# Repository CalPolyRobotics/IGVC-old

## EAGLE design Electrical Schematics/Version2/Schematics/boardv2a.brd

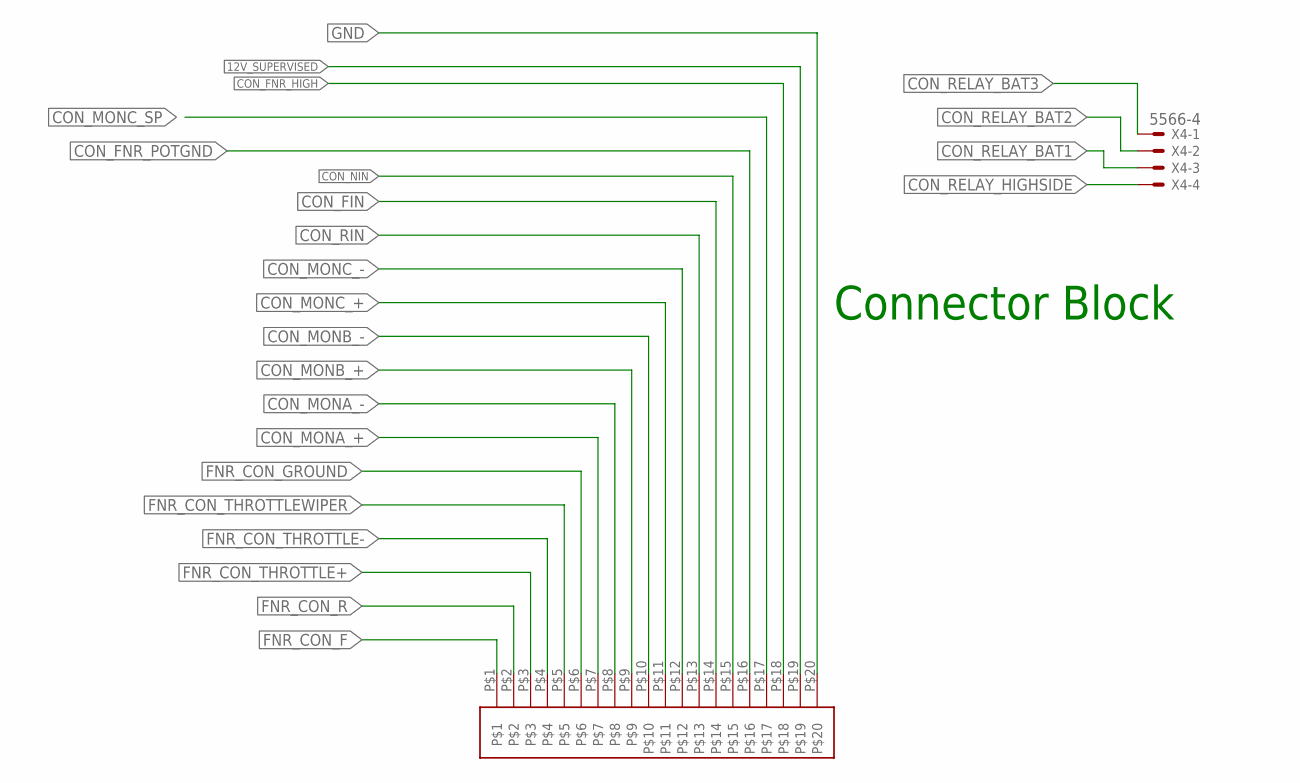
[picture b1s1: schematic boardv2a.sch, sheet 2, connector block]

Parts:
U$5: 34830-2001
X4: 5566-4

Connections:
12V_SUPERVISED: U$5.P$19; also elsewhere on the board
CON_FIN: U$5.P$14; also elsewhere on the board
CON_FNR_HIGH: U$5.P$18; also elsewhere on the board
CON_FNR_POTGND: U$5.P$16; also elsewhere on the board
CON_MONA_+: U$5.P$7; also elsewhere on the board
CON_MONA_-: U$5.P$8; also elsewhere on the board
CON_MONB_+: U$5.P$9; also elsewhere on the board
CON_MONB_-: U$5.P$10; also elsewhere on the board
CON_MONC_+: U$5.P$11; also elsewhere on the board
CON_MONC_-: U$5.P$12; also elsewhere on the board
CON_MONC_SP: U$5.P$17; also elsewhere on the board
CON_NIN: U$5.P$15; also elsewhere on the board
CON_RELAY_BAT1: X4.3; also elsewhere on the board
CON_RELAY_BAT2: X4.2; also elsewhere on the board
CON_RELAY_BAT3: X4.1; also elsewhere on the board
CON_RELAY_HIGHSIDE: X4.4
CON_RIN: U$5.P$13; also elsewhere on the board
FNR_CON_F: U$5.P$1; also elsewhere on the board
FNR_CON_GROUND: U$5.P$6
FNR_CON_R: U$5.P$2; also elsewhere on the board
FNR_CON_THROTTLE+: U$5.P$3; also elsewhere on the board
FNR_CON_THROTTLE-: U$5.P$4; also elsewhere on the board
FNR_CON_THROTTLEWIPER: U$5.P$5; also elsewhere on the board
GND: U$5.P$20; also elsewhere on the board

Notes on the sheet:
Connector Block

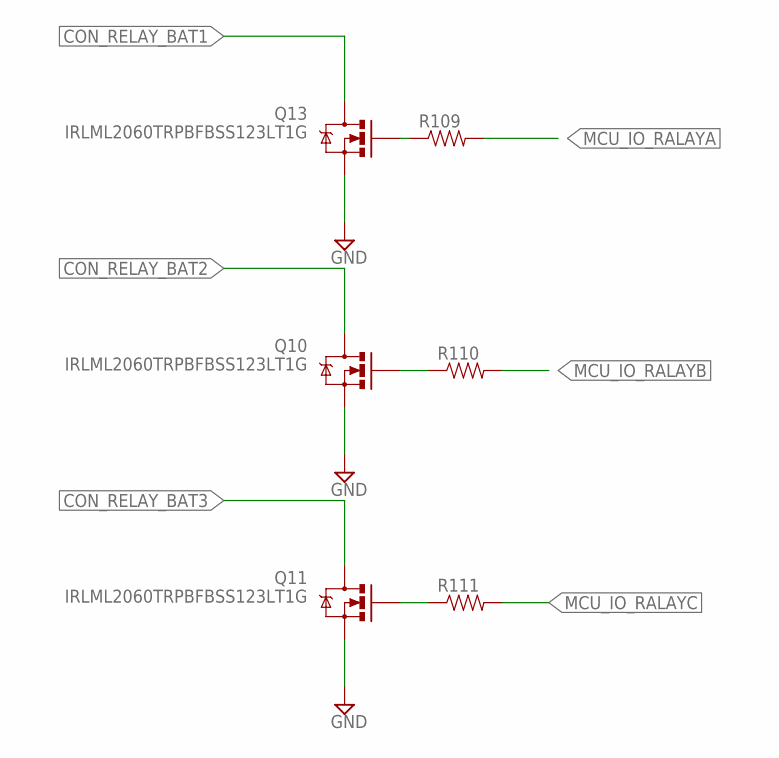
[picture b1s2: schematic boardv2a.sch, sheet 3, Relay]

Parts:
Q10, Q11, Q13: IRLML2060TRPBFBSS123LT1G; SOT23-3
R109, R110, R111: RESISTOR0603-RES; 0603-RES

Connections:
CON_RELAY_BAT1: Q13.3 (D); also elsewhere on the board
CON_RELAY_BAT2: Q10.3 (D); also elsewhere on the board
CON_RELAY_BAT3: Q11.3 (D); also elsewhere on the board
GND: Q10.2 (S), Q11.2 (S), Q13.2 (S); also elsewhere on the board
MCU_IO_RALAYA: R109.2; also elsewhere on the board
MCU_IO_RALAYB: R110.2; also elsewhere on the board
MCU_IO_RALAYC: R111.2; also elsewhere on the board
unnamed: Q13.1 (G), R109.1
unnamed: Q11.1 (G), R111.1
unnamed: Q10.1 (G), R110.1

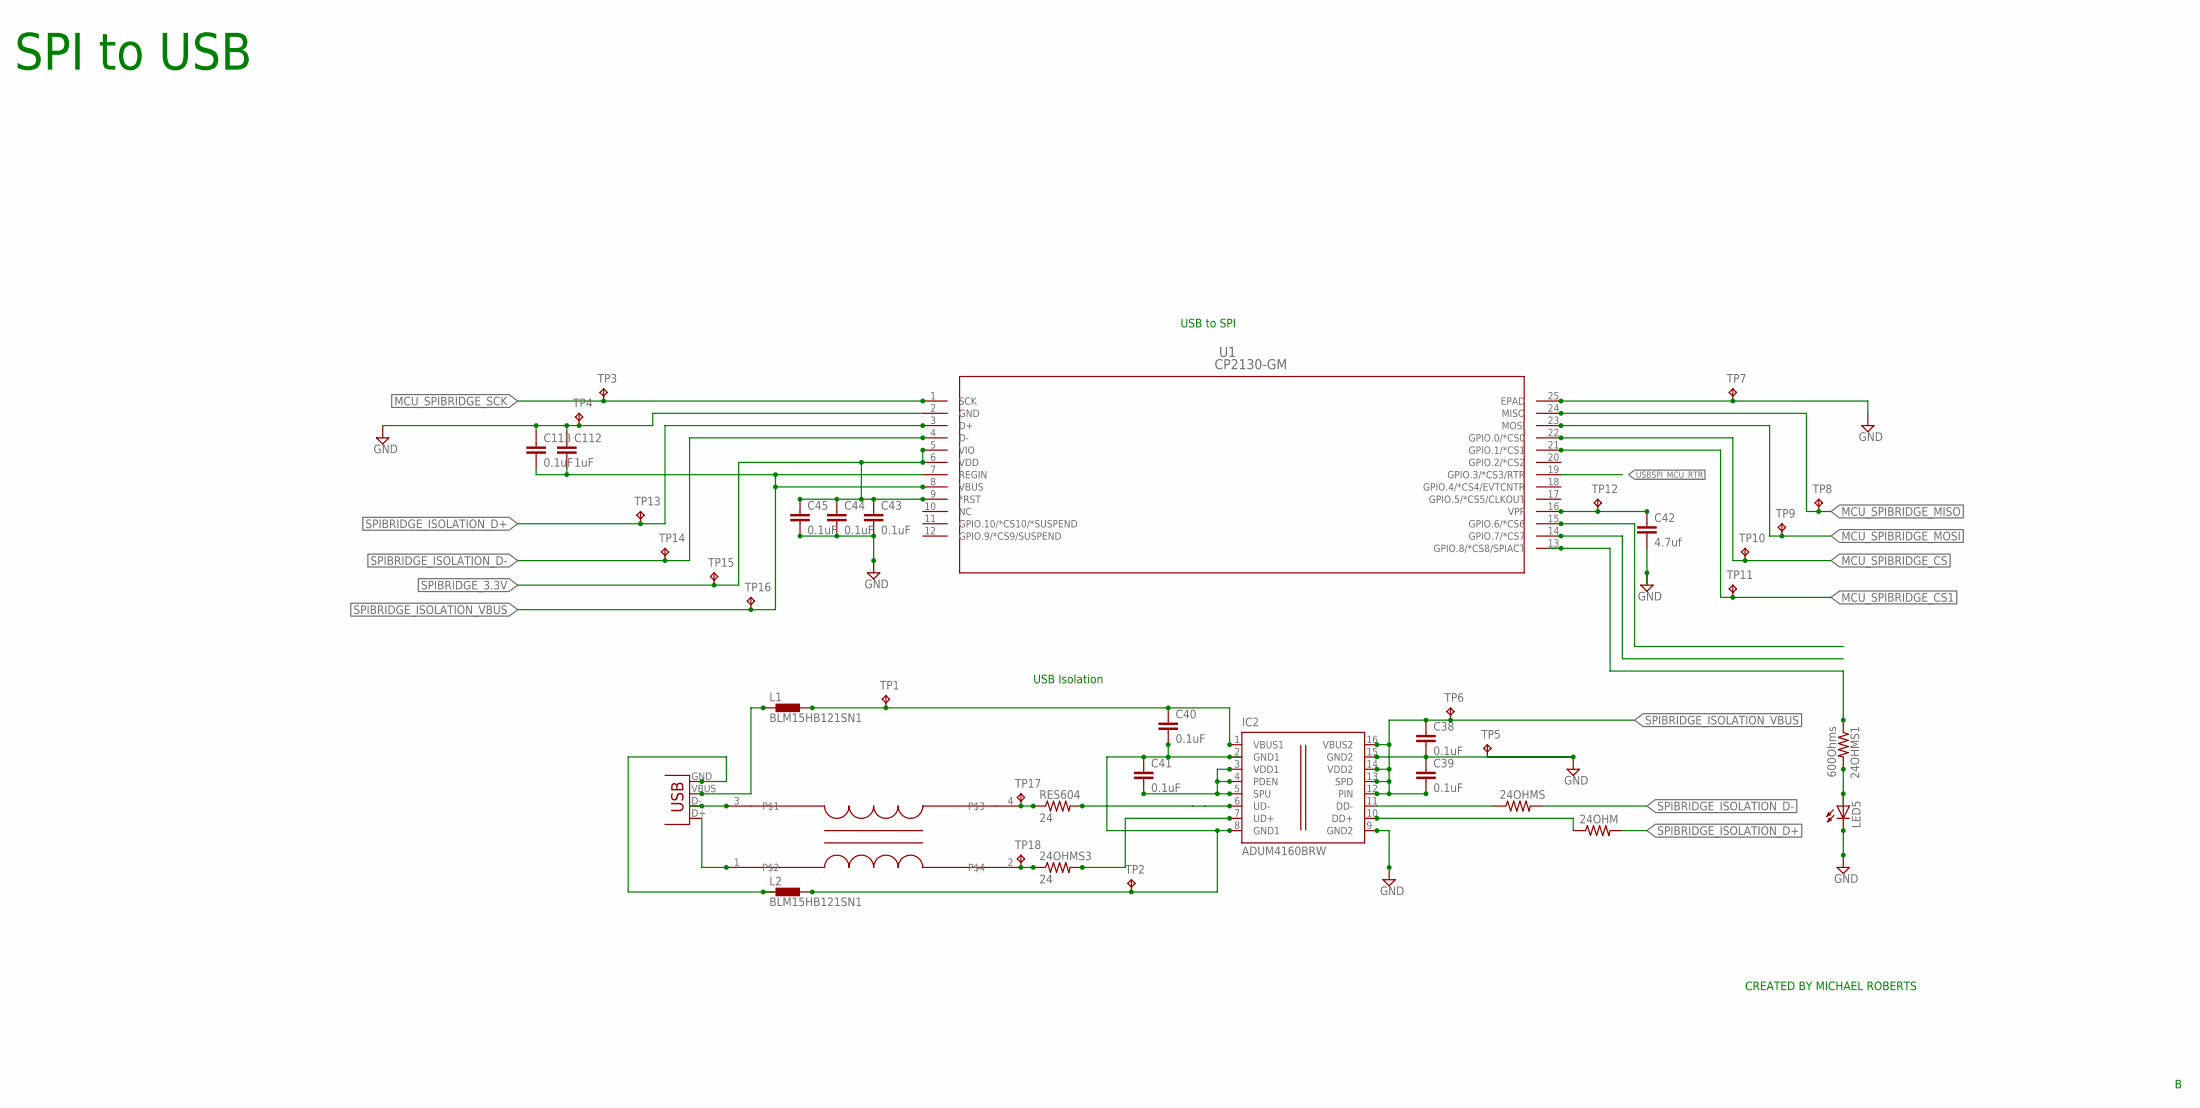
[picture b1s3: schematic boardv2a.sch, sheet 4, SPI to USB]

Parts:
24OHM, 24OHMS: RESISTOR0603-RES; 0603-RES
24OHMS1: 600Ohms; 0603-RES
24OHMS3: 24; 0603-RES
C38, C39, C40, C41, C43, C44, C45, C113: 0.1uF; C0603
C42: 4.7uf; C0603
C112: 1uF; C0603
IC2: ADUM4160BRW; SO16W
JP81: USB-B; USB-B-PTH
L1, L2: BLM15HB121SN1; 0402
LED5: LED_E; LED_1206
RES604: 24; 0603-RES
TP1, TP2, TP3, TP4, TP5, TP6, TP7, TP12, TP13, TP14, TP15, TP16: TPB1,27; B1,27
TP8, TP9, TP10, TP11, TP17, TP18: TPB2,54; B2,54
U1: CP2130-GM; QFN24_4X4
U$8: ACM3225-2P

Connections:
GND: C38.2, C39.1, C42.2, C43.2, C44.2, C45.2, C112.1, C113.1, IC2.9 (GND2), IC2.15 (GND2), LED5.C, TP4.TP, TP5.TP, TP7.TP, U1.2 (GND), U1.25 (EPAD); also elsewhere on the board
MCU_SPIBRIDGE_CS: TP10.TP, U1.22 (GPIO.0/*CS0); also elsewhere on the board
MCU_SPIBRIDGE_CS1: TP11.TP, U1.21 (GPIO.1/*CS1)
MCU_SPIBRIDGE_MISO: TP8.TP, U1.24 (MISO); also elsewhere on the board
MCU_SPIBRIDGE_MOSI: TP9.TP, U1.23 (MOSI); also elsewhere on the board
MCU_SPIBRIDGE_SCK: TP3.TP, U1.1 (SCK); also elsewhere on the board
unnamed: 24OHMS.1, IC2.11 (DD-)
unnamed: 24OHMS3.2, IC2.7 (UD+)
unnamed: C40.2, C41.1, IC2.2 (GND1), IC2.8 (GND1), L2.2, TP2.TP
unnamed: C40.1, IC2.1 (VBUS1), L1.2, TP1.TP
unnamed: JP81.D-, U$8.3
unnamed: JP81.D+, U$8.1
unnamed: JP81.GND, L2.1
unnamed: C41.2, IC2.3 (VDD1), IC2.4 (PDEN), IC2.5 (SPU)
unnamed: C42.1, TP12.TP, U1.16 (VPP)
unnamed: JP81.VBUS, L1.1
unnamed: 24OHMS1.1, U1.13 (GPIO.8/*CS8/SPIACT)
unnamed: 24OHMS1.2, LED5.A
unnamed: IC2.6 (UD-), RES604.2
unnamed: RES604.1, TP17.TP, U$8.4
unnamed: 24OHMS3.1, TP18.TP, U$8.2
unnamed: 24OHM.1, IC2.10 (DD+)
SPIBRIDGE_3.3V: C43.1, C44.1, C45.1, TP15.TP, U1.5 (VIO), U1.6 (VDD), U1.9 (*RST)
SPIBRIDGE_ISOLATION_D+: 24OHM.2, TP13.TP, U1.3 (D+)
SPIBRIDGE_ISOLATION_D-: 24OHMS.2, TP14.TP, U1.4 (D-)
SPIBRIDGE_ISOLATION_VBUS: C38.1, C39.2, C112.2, C113.2, IC2.12 (PIN), IC2.13 (SPD), IC2.14 (VDD2), IC2.16 (VBUS2), TP6.TP, TP16.TP, U1.7 (REGIN), U1.8 (VBUS)
USBSPI_MCU_RTR: U1.19 (GPIO.3/*CS3/RTR); also elsewhere on the board

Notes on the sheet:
USB Isolation
USB to SPI
SPI to USB
CREATED BY MICHAEL ROBERTS

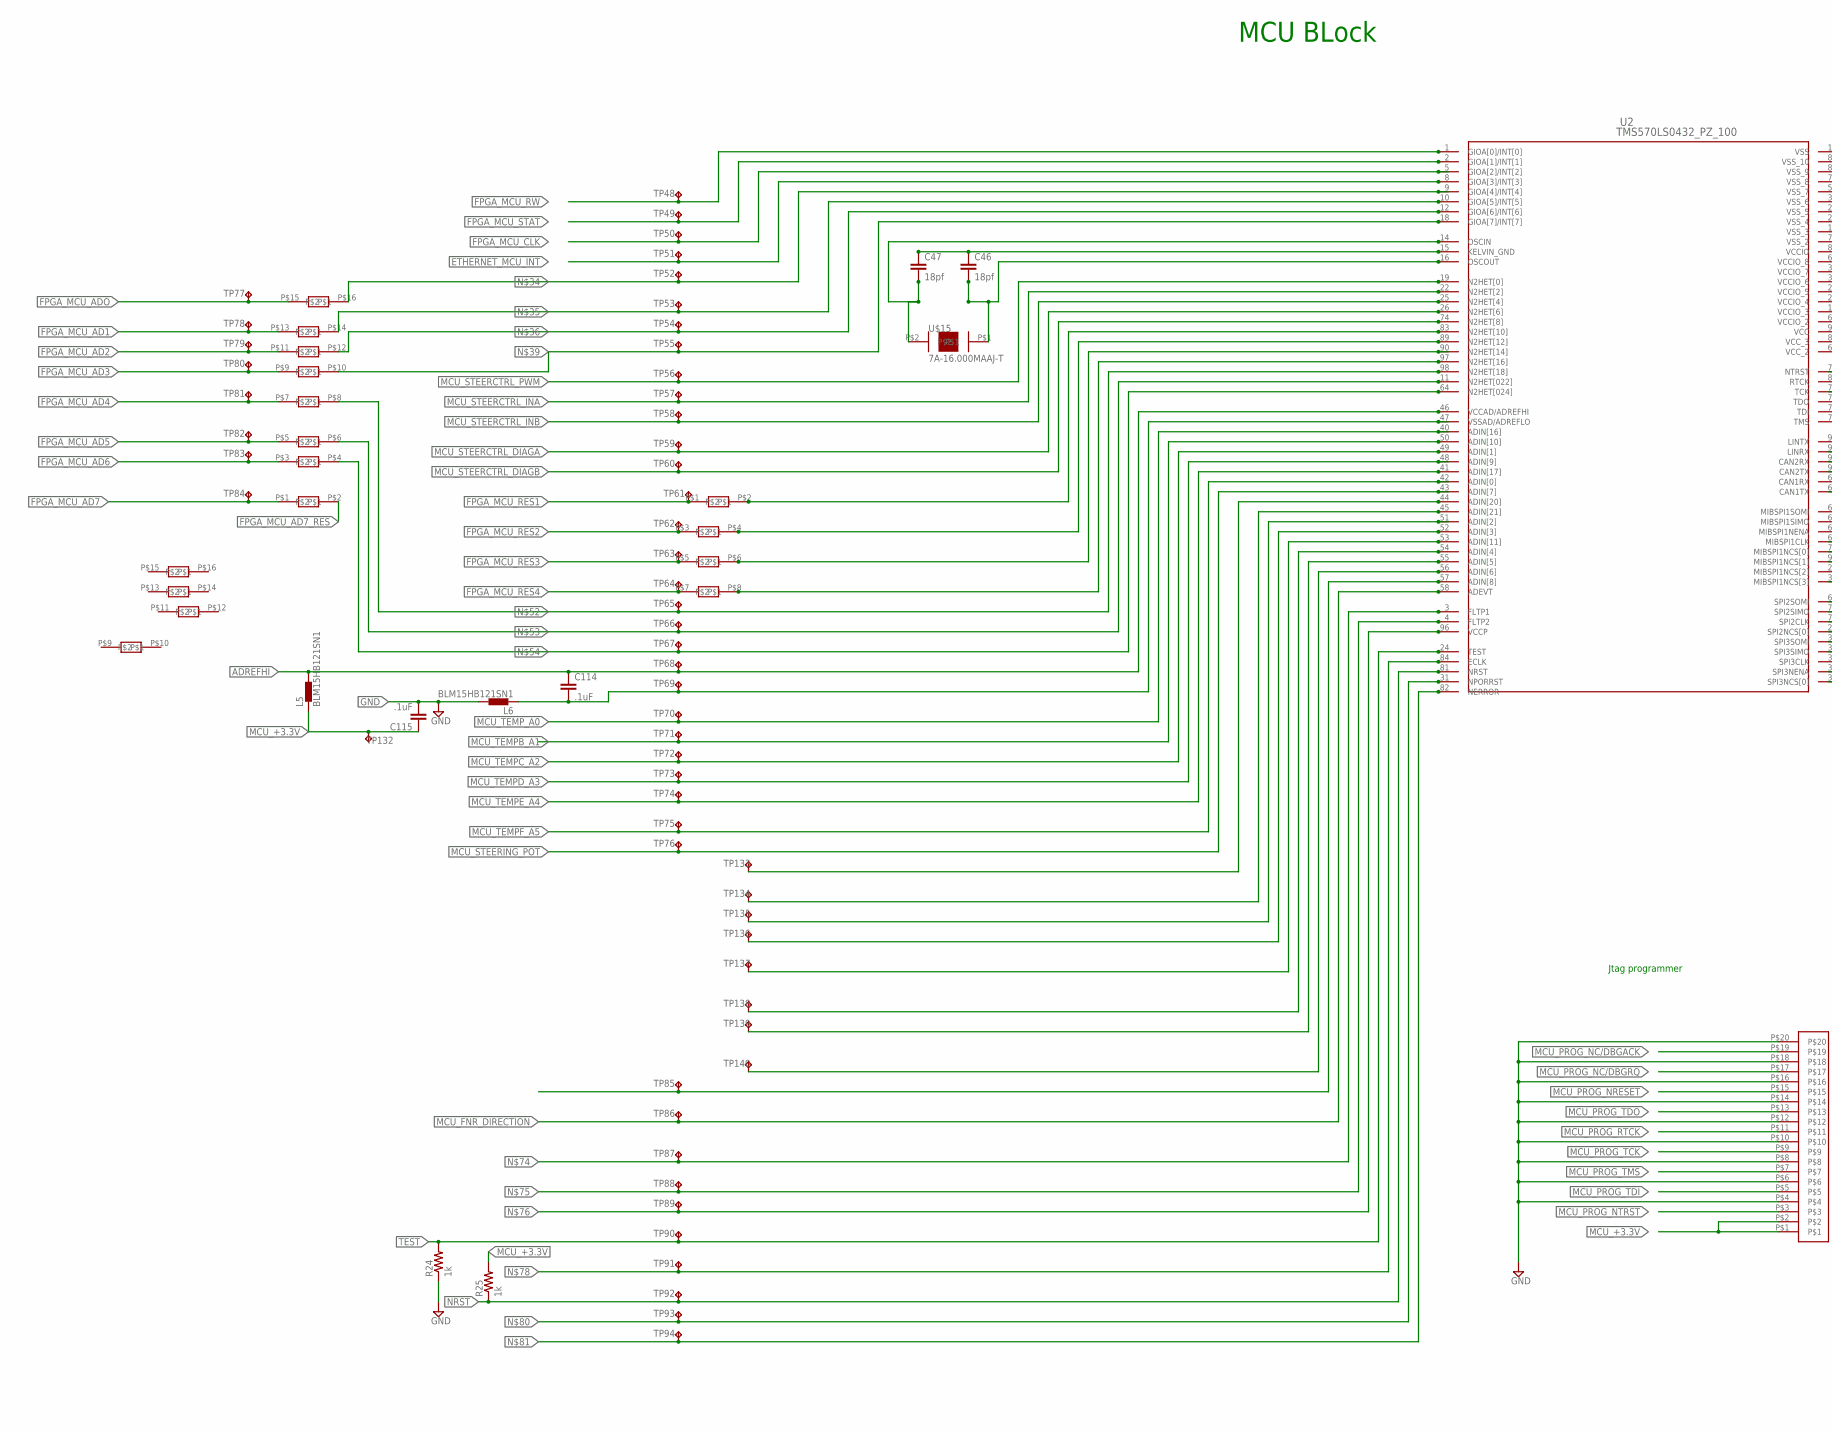
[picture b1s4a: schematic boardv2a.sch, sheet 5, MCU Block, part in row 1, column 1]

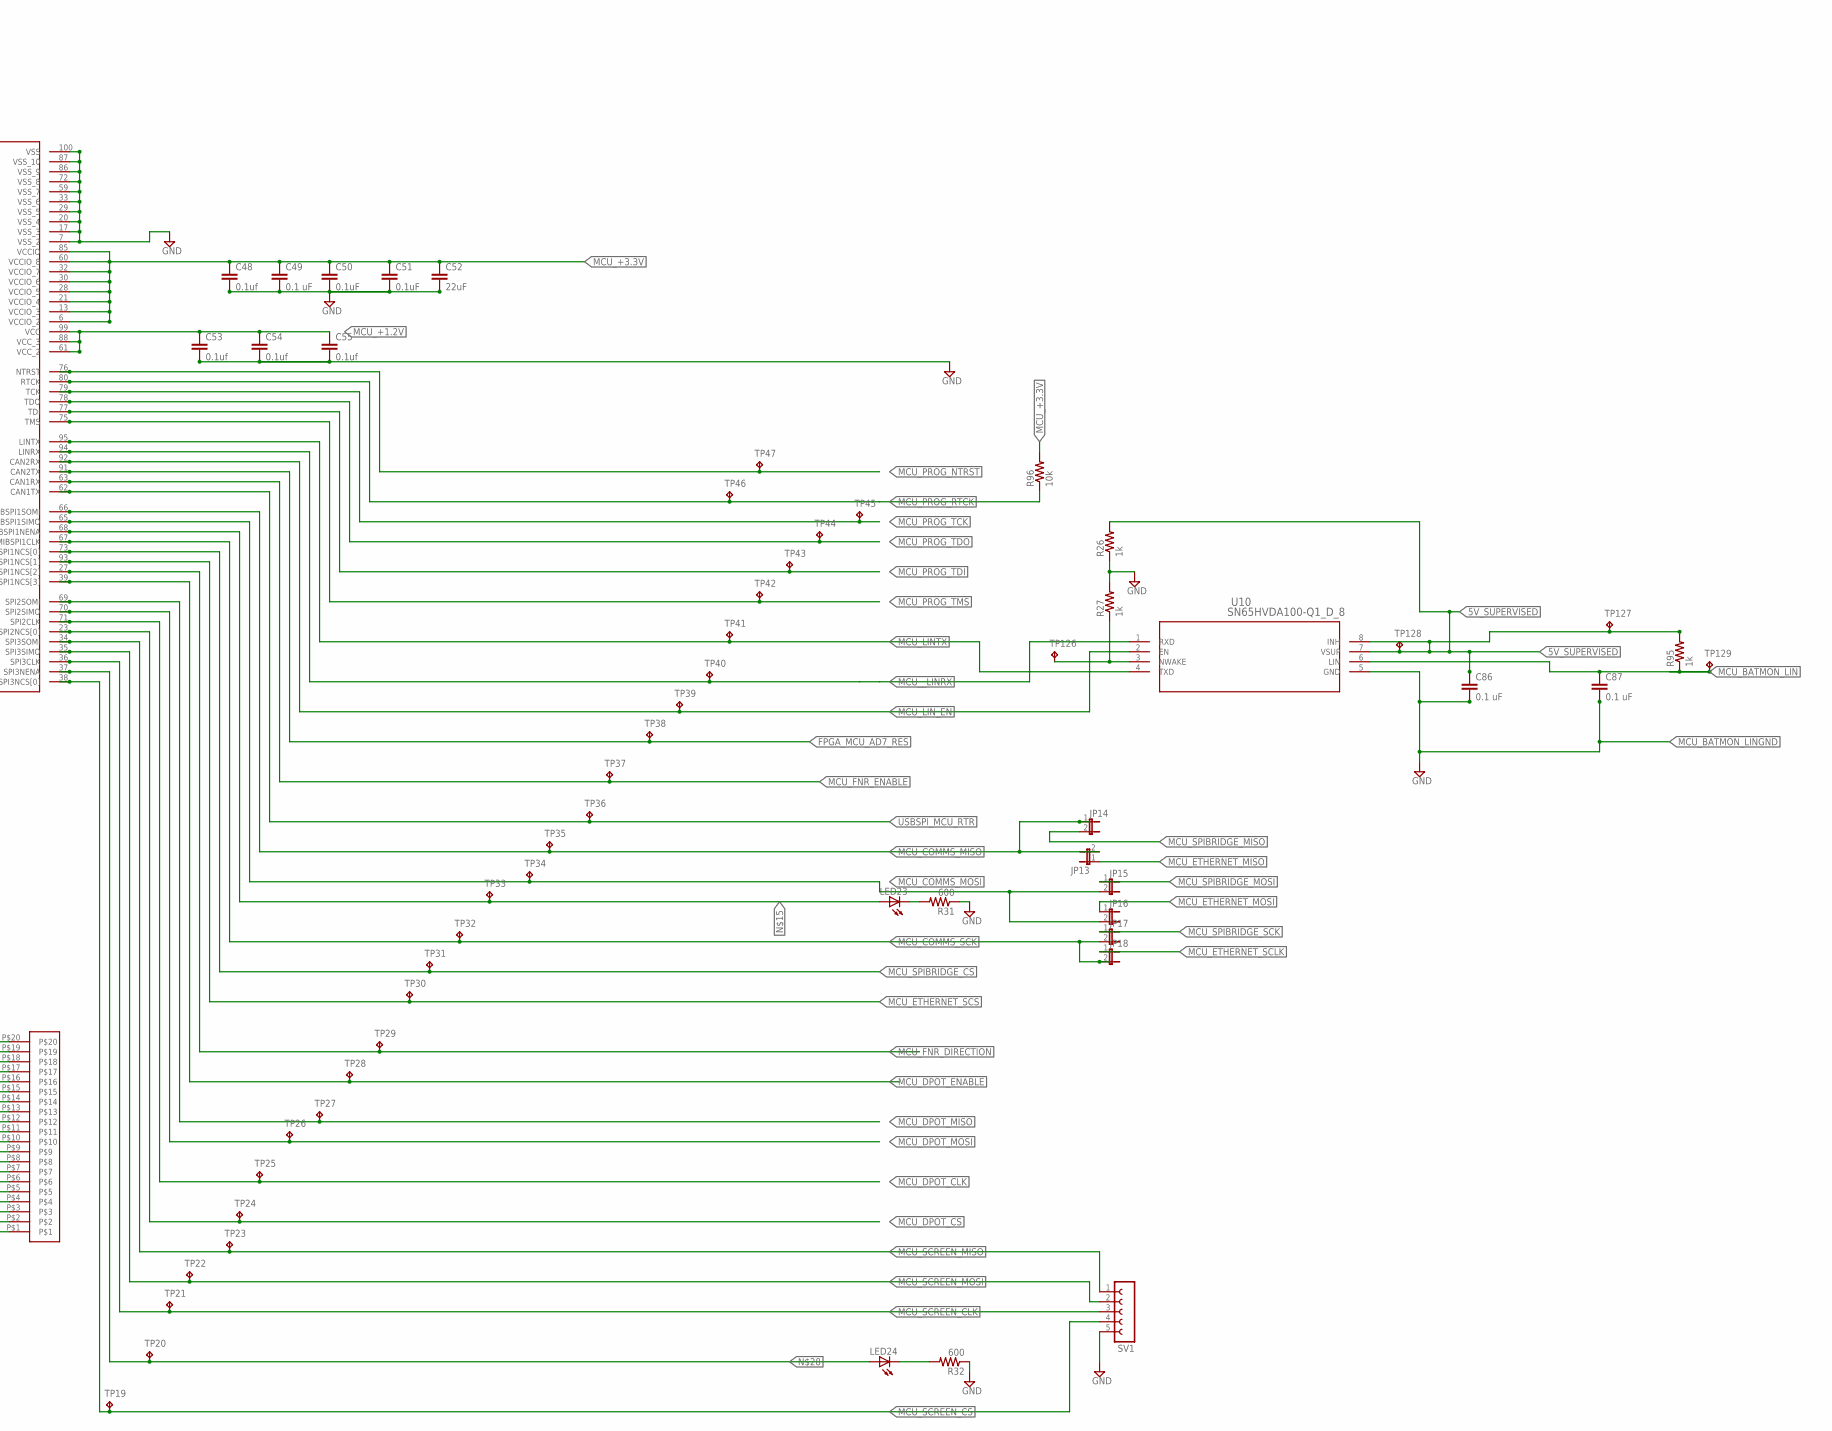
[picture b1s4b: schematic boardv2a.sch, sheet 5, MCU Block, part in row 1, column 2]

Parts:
C46, C47: 18pf; C0402
C48, C53, C54, C55: 0.1uf; C0402
C49, C86, C87: 0.1 uF; C0402
C50, C51: 0.1uF; C0402
C52: 22uF; C0402
C114, C115: .1uF; C0402
JP13, JP14, JP15, JP16, JP17, JP18: JP1E; JP1
L5, L6: BLM15HB121SN1; 0402
LED23, LED24: LED_E; LED_1206
R24, R25, R26, R27, R95: 1k; 0603-RES
R31, R32: 600; 0603-RES
R96: 10k; 0603-RES
SV1: FE05-1
TP19, TP20, TP21, TP22, TP23, TP24, TP25, TP26, TP27, TP28, TP29, TP30, TP31, TP32, TP33, TP34, TP35, TP36, TP37, TP38, TP39, TP40, TP41, TP42, TP43, TP44, TP45, TP46, TP47, TP48, TP49, TP50, TP51, TP52, TP53, TP54, TP55, TP56, TP57, TP58, TP59, TP60, TP61, TP62, TP63, TP64, TP65, TP66, TP67, TP68, TP69, TP70, TP71, TP72, TP73, TP74, TP75, TP76, TP77, TP78, TP79, TP80, TP81, TP82, TP83, TP84, TP85, TP86, TP87, TP88, TP89, TP90, TP91, TP92, TP93, TP94, TP126, TP127, TP128, TP129, TP132: TPB2,54; B2,54
TP133, TP134, TP135, TP136, TP137, TP138, TP139, TP140: TPPAD1-13; P1-13
U2: TMS570LS0432_PZ_100; PZ100
U10: SN65HVDA100-Q1_D_8; D8
U$4, U$32: RHM1620CT-ND; MNR18
U$9: JTAG20PIN; 15-80-0201
U$15: 7A-16.000MAAJ-T; 2-SMD

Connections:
5V_SUPERVISED: C86.1, R26.2, R95.2, TP127.TP, TP128.TP, U10.7 (VSUP), U10.8 (INH); also elsewhere on the board
ADREFHI: C114.1, L5.2, TP68.TP, U2.46 (VCCAD/ADREFHI)
ETHERNET_MCU_INT: TP51.TP, U2.8 (GIOA[3]/INT[3]); also elsewhere on the board
FPGA_MCU_AD1: TP78.TP, U$4.P$13; also elsewhere on the board
FPGA_MCU_AD2: TP79.TP, U$4.P$11; also elsewhere on the board
FPGA_MCU_AD3: TP80.TP, U$4.P$9; also elsewhere on the board
FPGA_MCU_AD4: TP81.TP, U$4.P$7; also elsewhere on the board
FPGA_MCU_AD5: TP82.TP, U$4.P$5; also elsewhere on the board
FPGA_MCU_AD6: TP83.TP, U$4.P$3; also elsewhere on the board
FPGA_MCU_AD7: TP84.TP, U$4.P$1; also elsewhere on the board
FPGA_MCU_AD7_RES: TP38.TP, U2.91 (CAN2TX), U$4.P$2
FPGA_MCU_ADO: TP77.TP, U$4.P$15; also elsewhere on the board
FPGA_MCU_CLK: TP50.TP, U2.5 (GIOA[2]/INT[2]); also elsewhere on the board
FPGA_MCU_RES1: TP61.TP, U$32.P$1; also elsewhere on the board
FPGA_MCU_RES1_RES: U2.83 (N2HET[10]), U$32.P$2
FPGA_MCU_RES2: TP62.TP, U$32.P$3; also elsewhere on the board
FPGA_MCU_RES2_RES: U2.89 (N2HET[12]), U$32.P$4
FPGA_MCU_RES3: TP63.TP, U$32.P$5; also elsewhere on the board
FPGA_MCU_RES3_RES: U2.90 (N2HET[14]), U$32.P$6
FPGA_MCU_RES4: TP64.TP, U$32.P$7; also elsewhere on the board
FPGA_MCU_RES4_RES: U2.97 (N2HET[16]), U$32.P$8
FPGA_MCU_RW: TP48.TP, U2.1 (GIOA[0]/INT[0]); also elsewhere on the board
FPGA_MCU_STAT: TP49.TP, U2.2 (GIOA[1]/INT[1]); also elsewhere on the board
GND: C48.2, C49.2, C50.2, C51.2, C52.2, C53.2, C54.2, C55.2, C115.2, L6.2, R24.1, R26.1, R27.2, R31.1, R32.1, SV1.5, U2.7 (VSS_2), U2.17 (VSS_3), U2.20 (VSS_4), U2.29 (VSS_5), U2.33 (VSS_6), U2.59 (VSS_7), U2.72 (VSS_8), U2.86 (VSS_9), U2.87 (VSS_10), U2.100 (VSS), U$9.P$4, U$9.P$6, U$9.P$8, U$9.P$10, U$9.P$12, U$9.P$14, U$9.P$16, U$9.P$18, U$9.P$20; also elsewhere on the board
MCU_+1.2V: C53.1, C54.1, C55.1, U2.61 (VCC_2), U2.88 (VCC_3), U2.99 (VCC)
MCU_+3.3V: C48.1, C49.1, C50.1, C51.1, C52.1, C115.1, L5.1, R25.2, R96.2, TP132.TP, U2.6 (VCCIO_2), U2.13 (VCCIO_3), U2.21 (VCCIO_4), U2.28 (VCCIO_5), U2.30 (VCCIO_6), U2.32 (VCCIO_7), U2.60 (VCCIO_8), U2.85 (VCCIO), U$9.P$1, U$9.P$2; also elsewhere on the board
MCU_A_GND: C114.2, L6.1, TP69.TP, U2.47 (VSSAD/ADREFLO); also elsewhere on the board
MCU_BATMON_LIN: C87.1, R95.1, TP129.TP, U10.6 (LIN); also elsewhere on the board
MCU_BATMON_LINGND: C86.2, C87.2, U10.5 (GND); also elsewhere on the board
MCU_COMMS_MISO: JP13.2, JP14.1, TP35.TP, U2.66 (MIBSPI1SOMI)
MCU_COMMS_MOSI: JP15.2, JP16.2, TP34.TP, U2.65 (MIBSPI1SIMO)
MCU_COMMS_SCK: JP17.2, JP18.2, TP32.TP, U2.67 (MIBSPI1CLK)
MCU_DPOT_CLK: TP25.TP, U2.71 (SPI2CLK); also elsewhere on the board
MCU_DPOT_CS: TP24.TP, U2.23 (SPI2NCS[0]); also elsewhere on the board
MCU_DPOT_ENABLE: TP28.TP, U2.39 (MIBSPI1NCS[3]); also elsewhere on the board
MCU_DPOT_MISO: TP27.TP, U2.69 (SPI2SOMI); also elsewhere on the board
MCU_DPOT_MOSI: TP26.TP, U2.70 (SPI2SIMO); also elsewhere on the board
MCU_ETHERNET_MISO: JP13.1; also elsewhere on the board
MCU_ETHERNET_MOSI: JP16.1; also elsewhere on the board
MCU_ETHERNET_SCLK: JP18.1; also elsewhere on the board
MCU_ETHERNET_SCS: TP30.TP, U2.93 (MIBSPI1NCS[1]); also elsewhere on the board
MCU_FNR_DIRECTION: TP29.TP, TP86.TP, U2.27 (MIBSPI1NCS[2]), U2.58 (ADEVT); also elsewhere on the board
MCU_FNR_ENABLE: TP37.TP, U2.63 (CAN1RX); also elsewhere on the board
MCU_LINTX: TP41.TP, U2.95 (LINTX), U10.4 (TXD)
MCU_LIN_EN: TP39.TP, U2.92 (CAN2RX), U10.2 (EN)
MCU_PROG_NC/DBGACK: U$9.P$19
MCU_PROG_NC/DBGRQ: U$9.P$17
MCU_PROG_NRESET: U$9.P$15
MCU_PROG_NTRST: TP47.TP, U2.76 (NTRST), U$9.P$3
MCU_PROG_RTCK: R96.1, TP46.TP, U2.80 (RTCK), U$9.P$11
MCU_PROG_TCK: TP45.TP, U2.79 (TCK), U$9.P$9
MCU_PROG_TDI: TP43.TP, U2.77 (TDI), U$9.P$5
MCU_PROG_TDO: TP44.TP, U2.78 (TDO), U$9.P$13
MCU_PROG_TMS: TP42.TP, U2.75 (TMS), U$9.P$7
MCU_SCREEN_CLK: SV1.3, TP21.TP, U2.36 (SPI3CLK)
MCU_SCREEN_CS: SV1.4, TP19.TP, U2.38 (SPI3NCS[0])
MCU_SCREEN_MISO: SV1.1, TP23.TP, U2.34 (SPI3SOMI)
MCU_SCREEN_MOSI: SV1.2, TP22.TP, U2.35 (SPI3SIMO)
MCU_SPIBRIDGE_CS: TP31.TP, U2.73 (MIBSPI1NCS[0]); also elsewhere on the board
MCU_SPIBRIDGE_MISO: JP14.2; also elsewhere on the board
MCU_SPIBRIDGE_MOSI: JP15.1; also elsewhere on the board
MCU_SPIBRIDGE_SCK: JP17.1; also elsewhere on the board
MCU_STEERCTRL_DIAGA: TP59.TP, U2.26 (N2HET[6]); also elsewhere on the board
MCU_STEERCTRL_DIAGB: TP60.TP, U2.74 (N2HET[8]); also elsewhere on the board
MCU_STEERCTRL_INA: TP57.TP, U2.22 (N2HET[2]); also elsewhere on the board
MCU_STEERCTRL_INB: TP58.TP, U2.25 (N2HET[4]); also elsewhere on the board
MCU_STEERCTRL_PWM: TP56.TP, U2.19 (N2HET[0]); also elsewhere on the board
MCU_STEERING_POT: TP76.TP, U2.43 (ADIN[7]); also elsewhere on the board
MCU_TEMPB_A1: TP71.TP, U2.50 (ADIN[10]); also elsewhere on the board
MCU_TEMPC_A2: TP72.TP, U2.49 (ADIN[1]); also elsewhere on the board
MCU_TEMPD_A3: TP73.TP, U2.48 (ADIN[9]); also elsewhere on the board
MCU_TEMPE_A4: TP74.TP, U2.41 (ADIN[17]); also elsewhere on the board
MCU_TEMPF_A5: TP75.TP, U2.42 (ADIN[0]); also elsewhere on the board
MCU_TEMP_A0: TP70.TP, U2.40 (ADIN[16]); also elsewhere on the board
MCU__LINRX: TP40.TP, U2.94 (LINRX), U10.1 (RXD)
unnamed: LED23.A, TP33.TP, U2.68 (MIBSPI1NENA)
unnamed: LED23.C, R31.2
unnamed: LED24.C, R32.2
unnamed: LED24.A, TP20.TP, U2.37 (SPI3NENA)
unnamed: TP52.TP, U2.9 (GIOA[4]/INT[4]), U$4.P$16
unnamed: TP53.TP, U2.10 (GIOA[5]/INT[5]), U$4.P$14
unnamed: TP54.TP, U2.12 (GIOA[6]/INT[6]), U$4.P$12
unnamed: TP55.TP, U2.18 (GIOA[7]/INT[7]), U$4.P$10
unnamed: TP65.TP, U2.98 (N2HET[18]), U$4.P$8
unnamed: TP66.TP, U2.11 (N2HET[022]), U$4.P$6
unnamed: TP67.TP, U2.64 (N2HET[024]), U$4.P$4
unnamed: TP87.TP, U2.3 (FLTP1)
unnamed: TP88.TP, U2.4 (FLTP2)
unnamed: TP89.TP, U2.96 (VCCP)
unnamed: TP91.TP, U2.84 (ECLK)
unnamed: TP93.TP, U2.31 (NPORRST)
unnamed: TP94.TP, U2.82 (NERROR)
unnamed: R27.1, TP126.TP, U10.3 (NWAKE)
unnamed: C46.1, C47.1, U2.15 (KELVIN_GND)
unnamed: C47.2, U2.14 (OSCIN), U$15.P$2
unnamed: C46.2, U2.16 (OSCOUT), U$15.P$1
unnamed: TP85.TP, U2.57 (ADIN[8])
unnamed: TP133.TP, U2.44 (ADIN[20])
unnamed: TP134.TP, U2.45 (ADIN[21])
unnamed: TP135.TP, U2.51 (ADIN[2])
unnamed: TP136.TP, U2.52 (ADIN[3])
unnamed: TP137.TP, U2.53 (ADIN[11])
unnamed: TP138.TP, U2.54 (ADIN[4])
unnamed: TP139.TP, U2.55 (ADIN[5])
unnamed: TP140.TP, U2.56 (ADIN[6])
NRST: R25.1, TP92.TP, U2.81 (NRST)
TEST: R24.2, TP90.TP, U2.24 (TEST)
USBSPI_MCU_RTR: TP36.TP, U2.62 (CAN1TX); also elsewhere on the board

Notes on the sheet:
Jtag programmer
MCU BLock

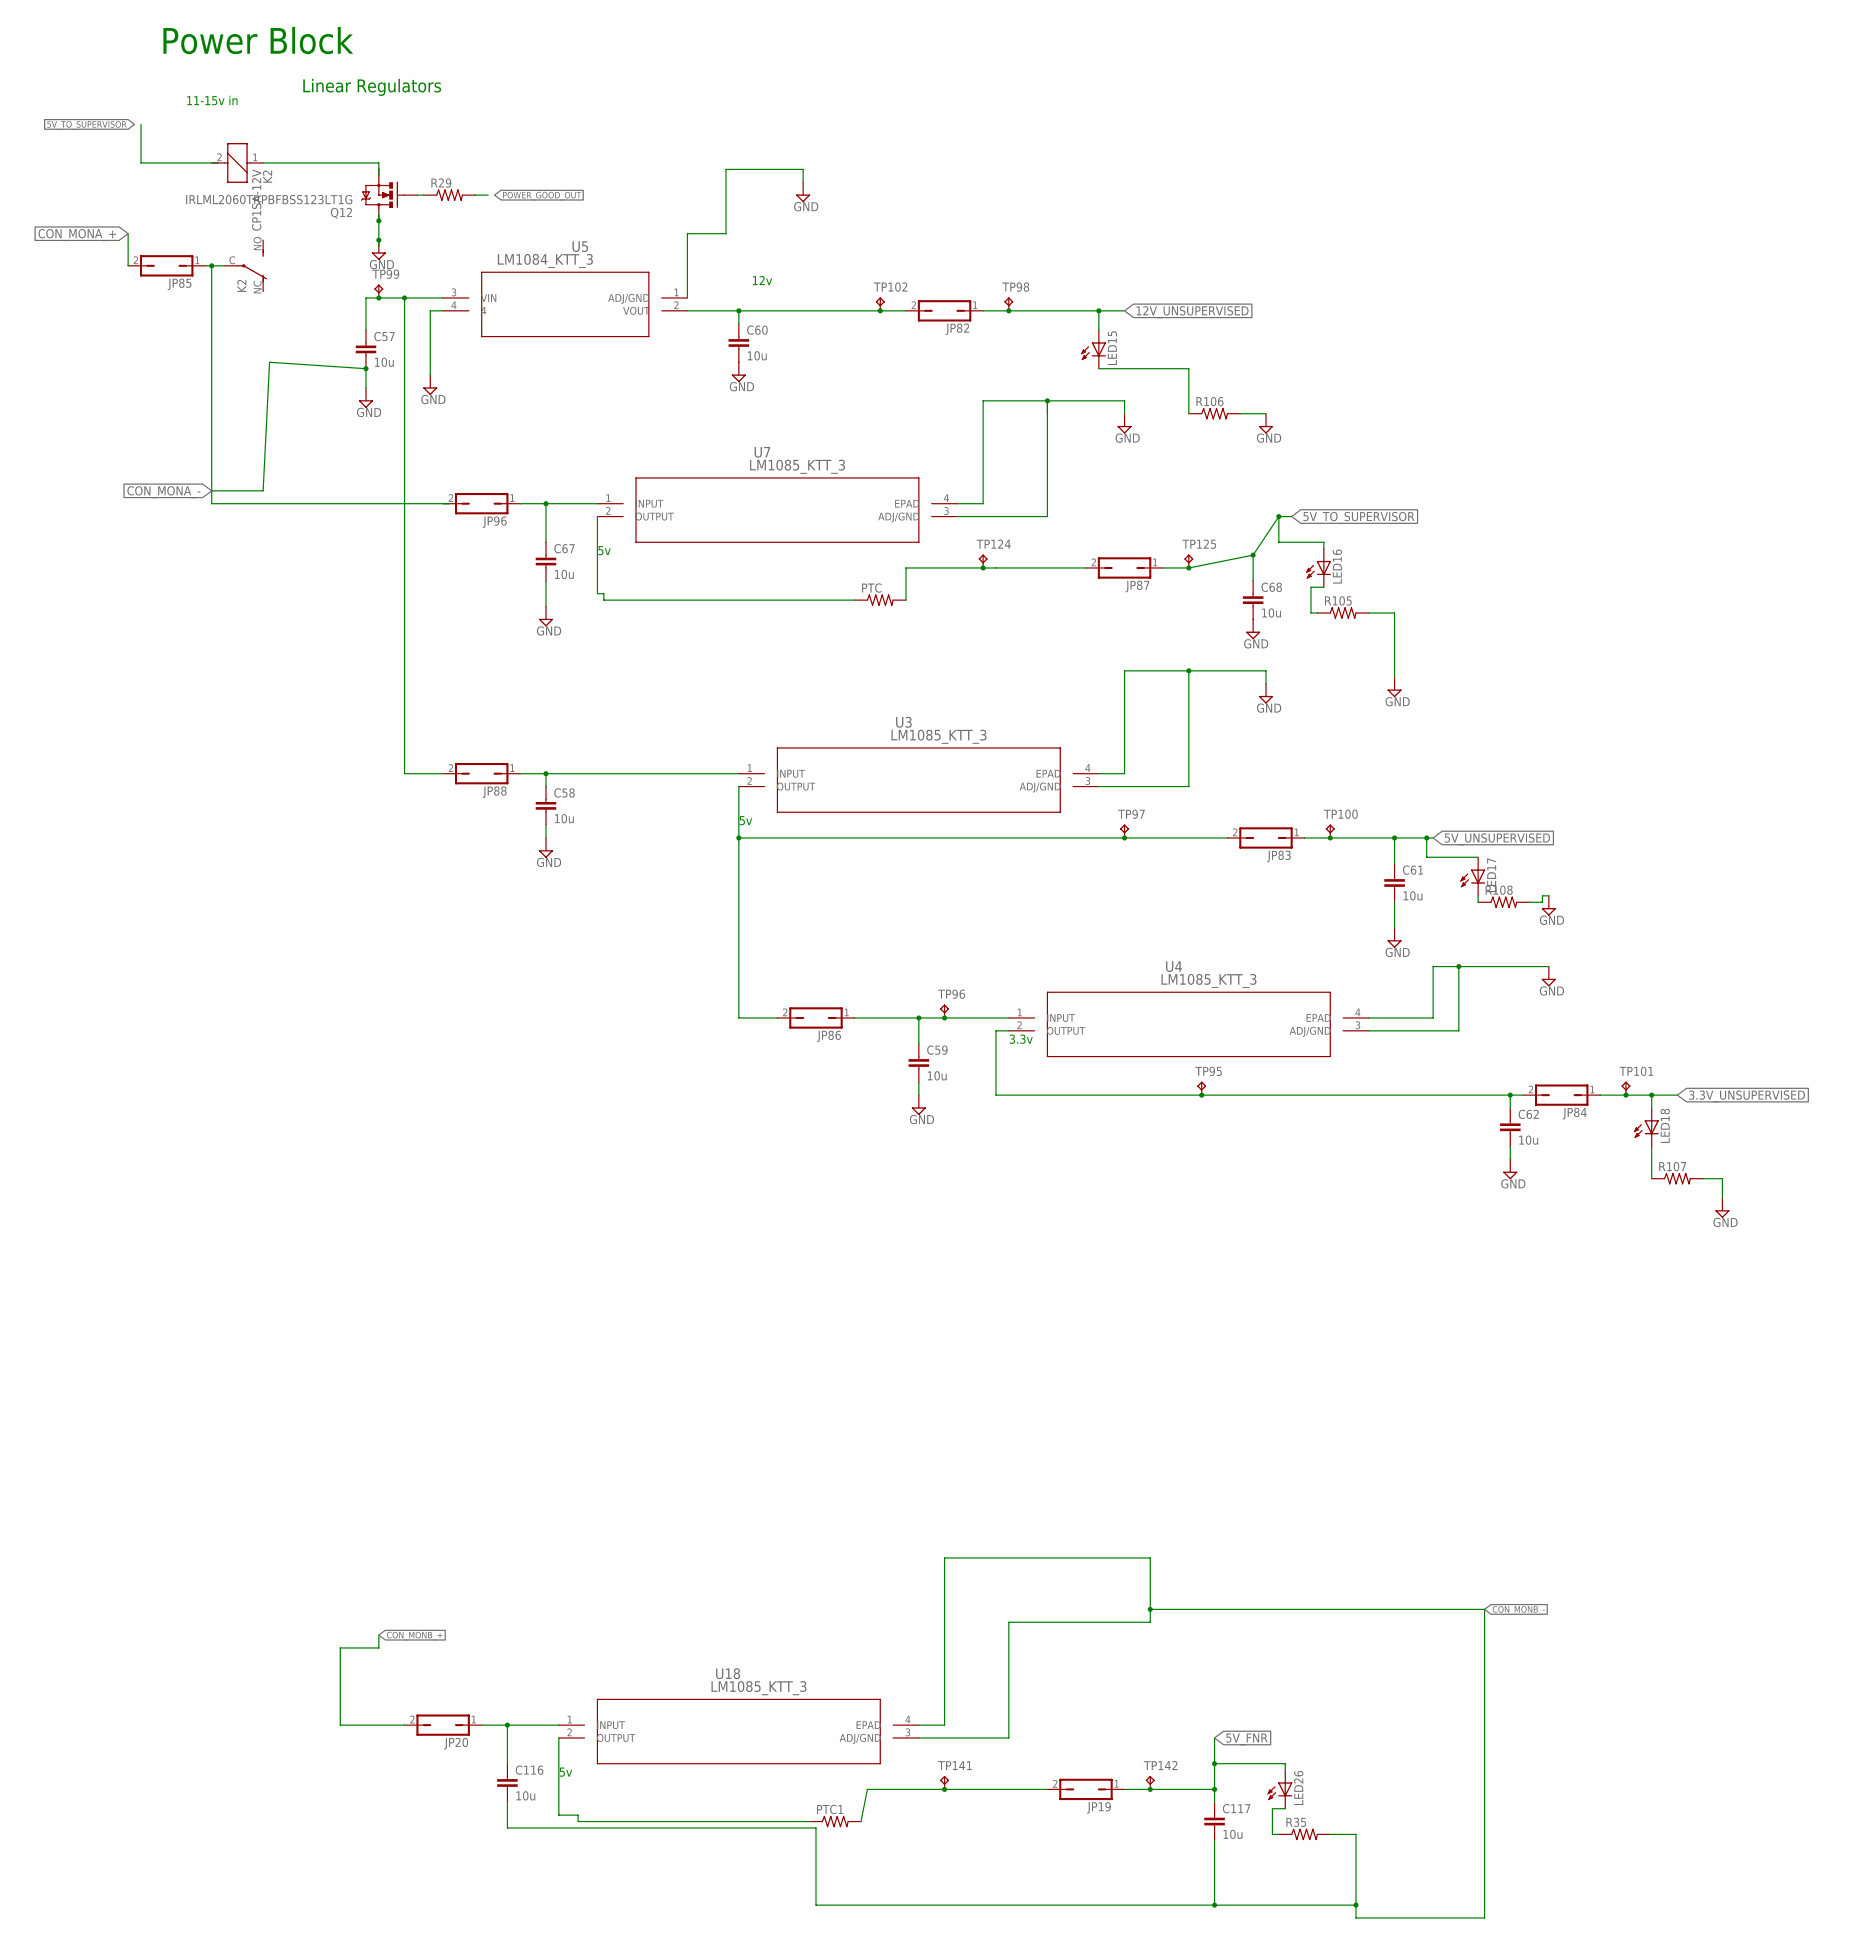
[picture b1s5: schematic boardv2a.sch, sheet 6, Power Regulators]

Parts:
C57, C58, C59, C60, C61, C62, C67, C68, C116, C117: 10u; C0603
JP19, JP20, JP82, JP83, JP84, JP85, JP86, JP87, JP88, JP96: JP1Q; JP1
K2: CP1SA-12V; CP1SA
LED15, LED16, LED17, LED18, LED26: LEDSML1206; SML1206
PTC, PTC1: R-US_R1206W; R1206W
Q12: IRLML2060TRPBFBSS123LT1G; SOT23-3
R29, R35, R105, R106, R107, R108: RESISTOR0603-RES; 0603-RES
TP95, TP96, TP97, TP98, TP99, TP100, TP101, TP102, TP124, TP125, TP141, TP142: TPB1,27; B1,27
U3, U4, U7, U18: LM1085_KTT_3; KTT3
U5: LM1084_KTT_3; TS3B

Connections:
3.3V_UNSUPERVISED: JP84.1, LED18.A, TP101.TP; also elsewhere on the board
5V_FNR: C117.1, JP19.1, LED26.A, TP142.TP; also elsewhere on the board
5V_TO_SUPERVISOR: C68.1, JP87.1, LED16.A, TP125.TP; also elsewhere on the board
5V_UNSUPERVISED: C61.1, JP83.1, LED17.A, TP100.TP; also elsewhere on the board
12V_UNSUPERVISED: JP82.1, LED15.A, TP98.TP; also elsewhere on the board
CON_MONA_+: JP85.2; also elsewhere on the board
CON_MONA_-: C57.2; also elsewhere on the board
CON_MONB_+: JP20.2; also elsewhere on the board
CON_MONB_-: C116.2, C117.2, R35.2, U18.3 (ADJ/GND), U18.4 (EPAD); also elsewhere on the board
GND: C58.2, C59.2, C60.2, C61.2, C62.2, C67.2, C68.2, Q12.3 (D), R105.2, R106.2, R107.2, R108.2, U3.3 (ADJ/GND), U3.4 (EPAD), U4.3 (ADJ/GND), U4.4 (EPAD), U5.1 (ADJ/GND), U5.4, U7.3 (ADJ/GND), U7.4 (EPAD); also elsewhere on the board
unnamed: JP19.2, PTC1.2, TP141.TP
unnamed: C116.1, JP20.1, U18.1 (INPUT)
unnamed: JP85.1, K2.C
unnamed: LED26.C, R35.1
unnamed: PTC1.1, U18.2 (OUTPUT)
unnamed: K2.1, Q12.2 (S)
unnamed: C60.1, JP82.2, TP102.TP, U5.2 (VOUT)
unnamed: C62.1, JP84.2, TP95.TP, U4.2 (OUTPUT)
unnamed: C59.1, JP86.1, TP96.TP, U4.1 (INPUT)
unnamed: JP87.2, PTC.2, TP124.TP
unnamed: C58.1, JP88.1, U3.1 (INPUT)
unnamed: C67.1, JP96.1, U7.1 (INPUT)
unnamed: LED15.C, R106.1
unnamed: LED16.C, R105.1
unnamed: LED17.C, R108.1
unnamed: LED18.C, R107.1
unnamed: JP83.2, JP86.2, TP97.TP, U3.2 (OUTPUT)
unnamed: PTC.1, U7.2 (OUTPUT)
POWER_GOOD_OUT: R29.2; also elsewhere on the board
POWER_GOOD_OUTD: Q12.1 (G), R29.1
VOLTAGEJMP_+_TO_INPUT_VREG: C57.1, JP88.2, TP99.TP, U5.3 (VIN)

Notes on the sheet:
11-15v in
12v
3.3v
Linear Regulators
Power Block

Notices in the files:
parts and their libraries:
SparkFun-Connectors: Licensing: Creative Commons ShareAlike 4.0 International - https://creativecommons.org/licenses/by-sa/4.0
ModularJackstehendungeschirmtWR-MJ: Copyright: Würth Elektronik
